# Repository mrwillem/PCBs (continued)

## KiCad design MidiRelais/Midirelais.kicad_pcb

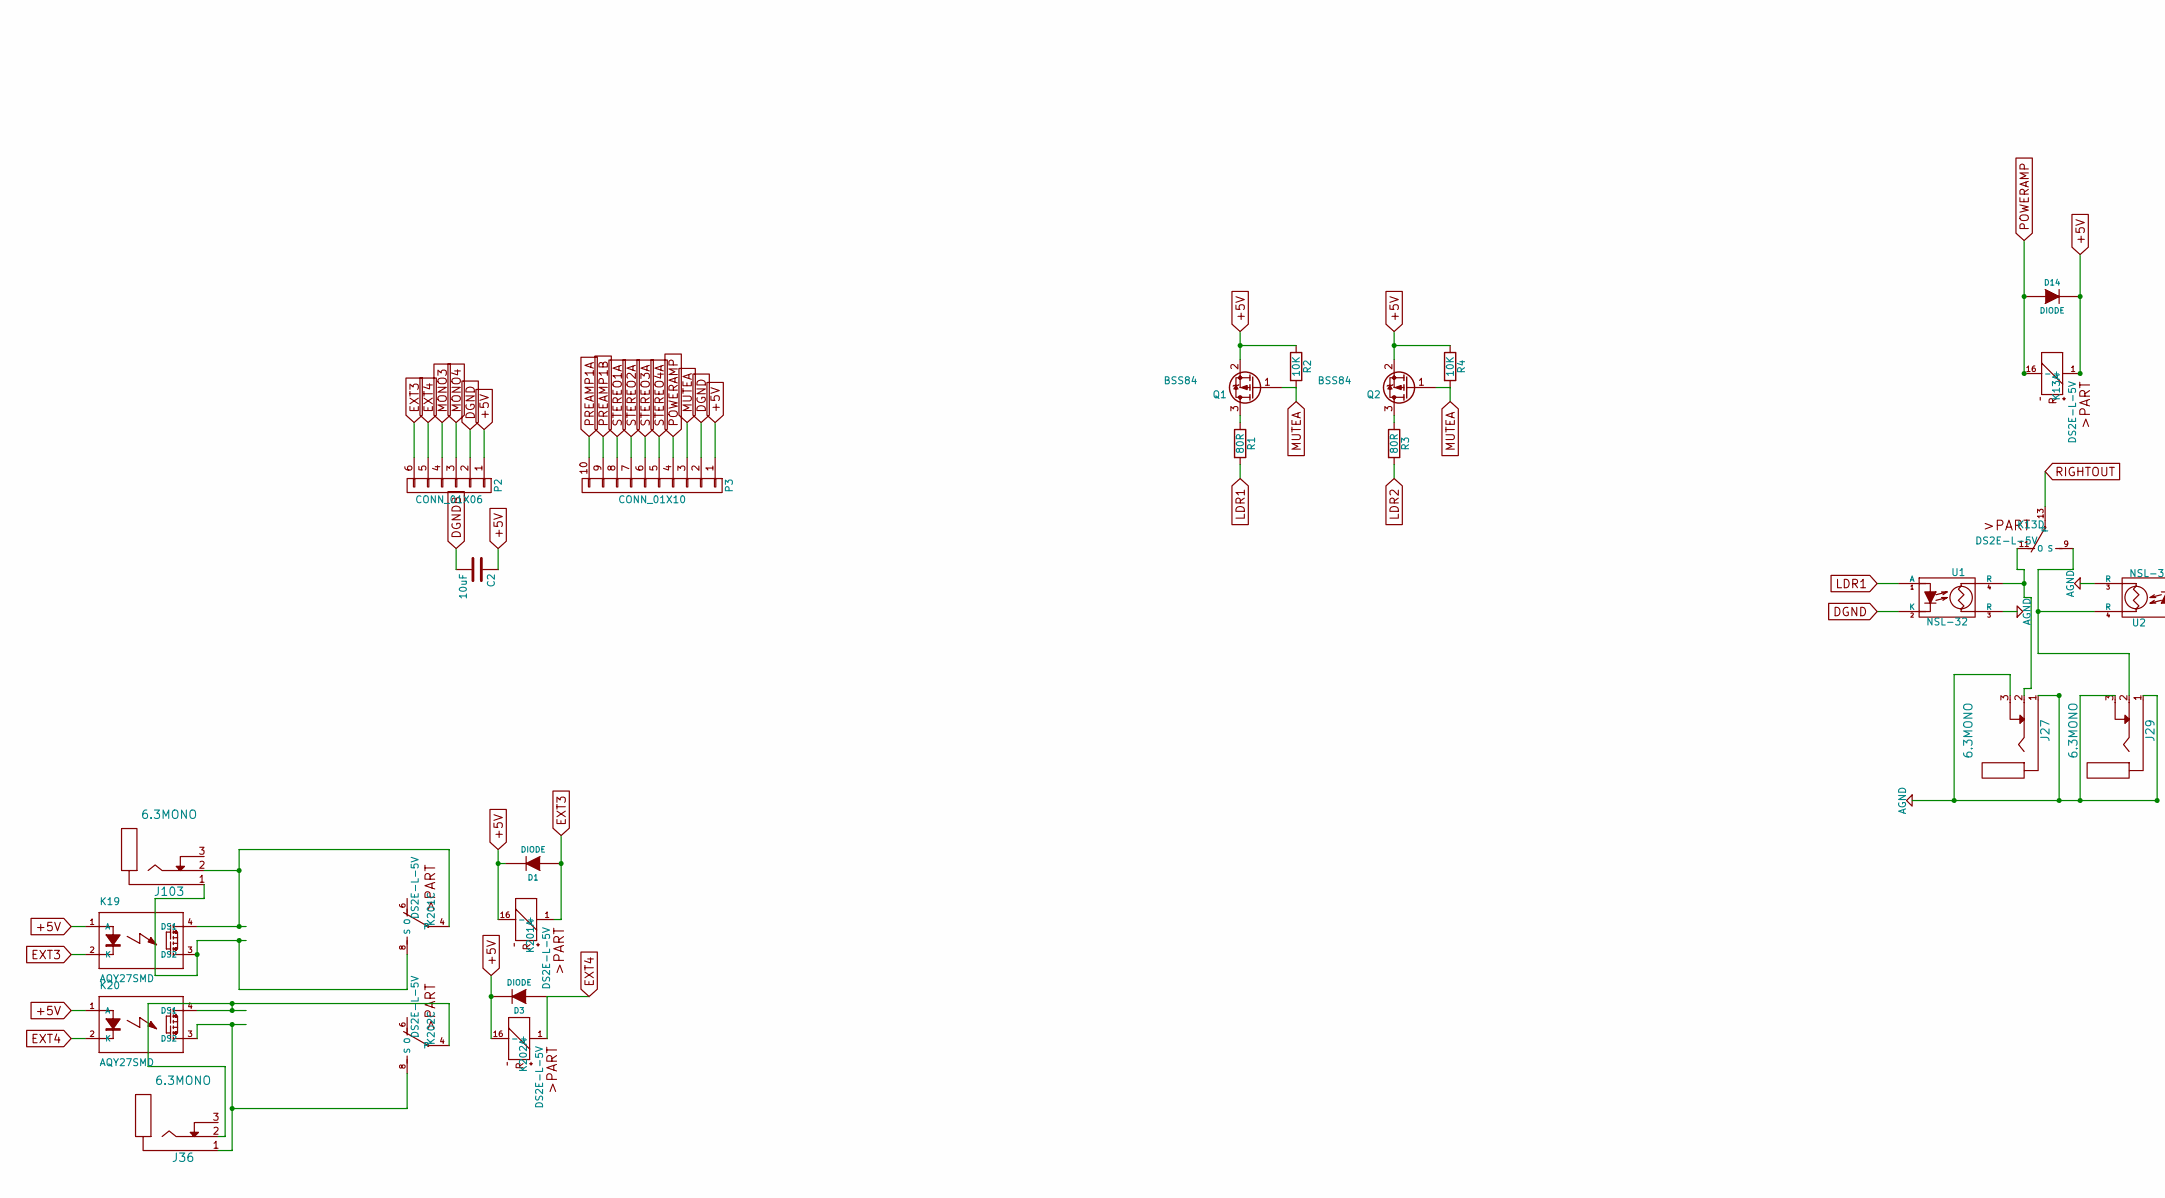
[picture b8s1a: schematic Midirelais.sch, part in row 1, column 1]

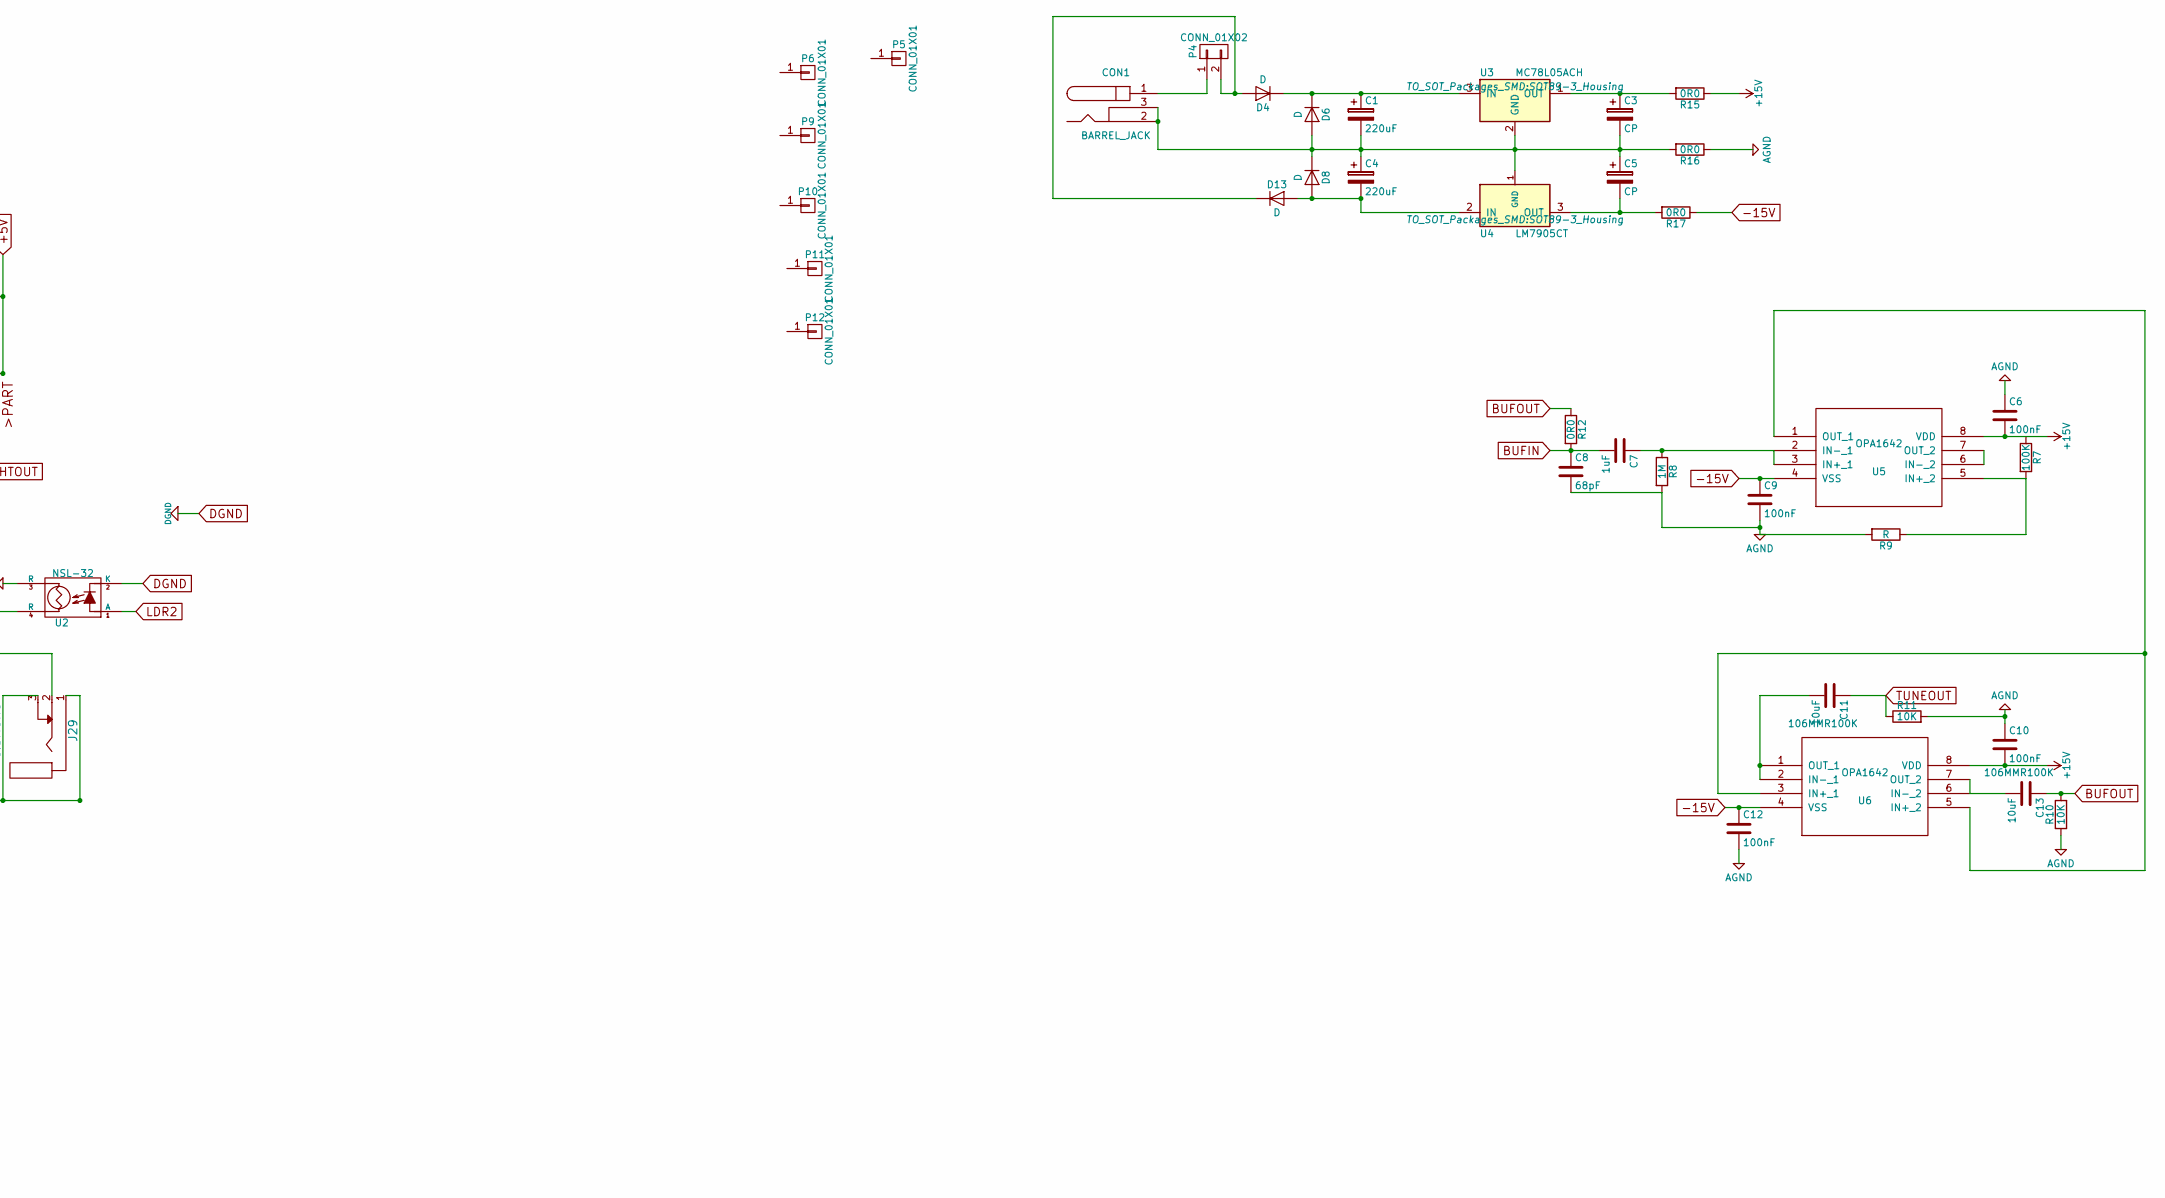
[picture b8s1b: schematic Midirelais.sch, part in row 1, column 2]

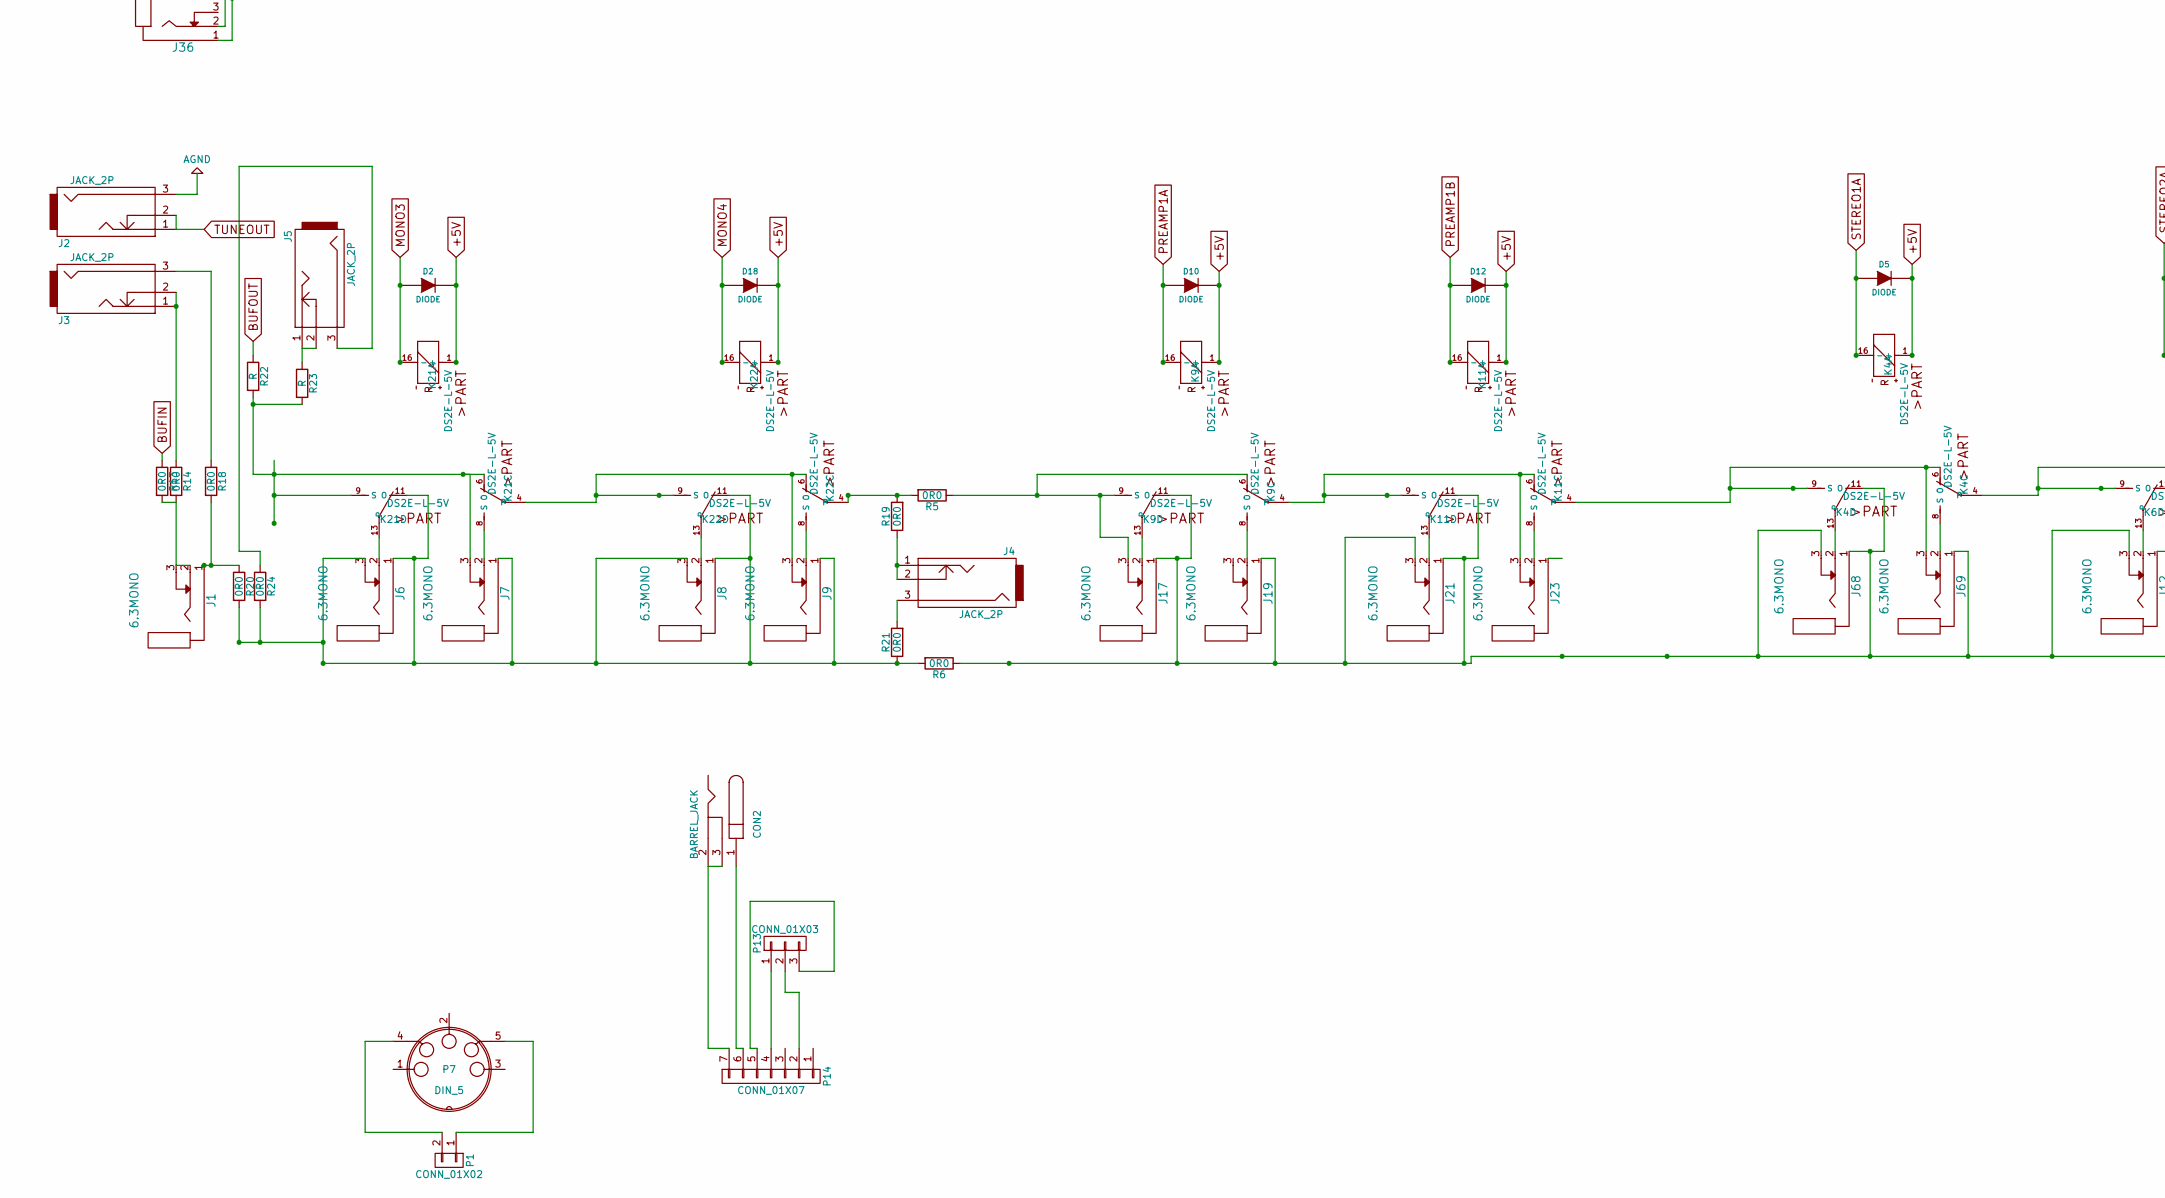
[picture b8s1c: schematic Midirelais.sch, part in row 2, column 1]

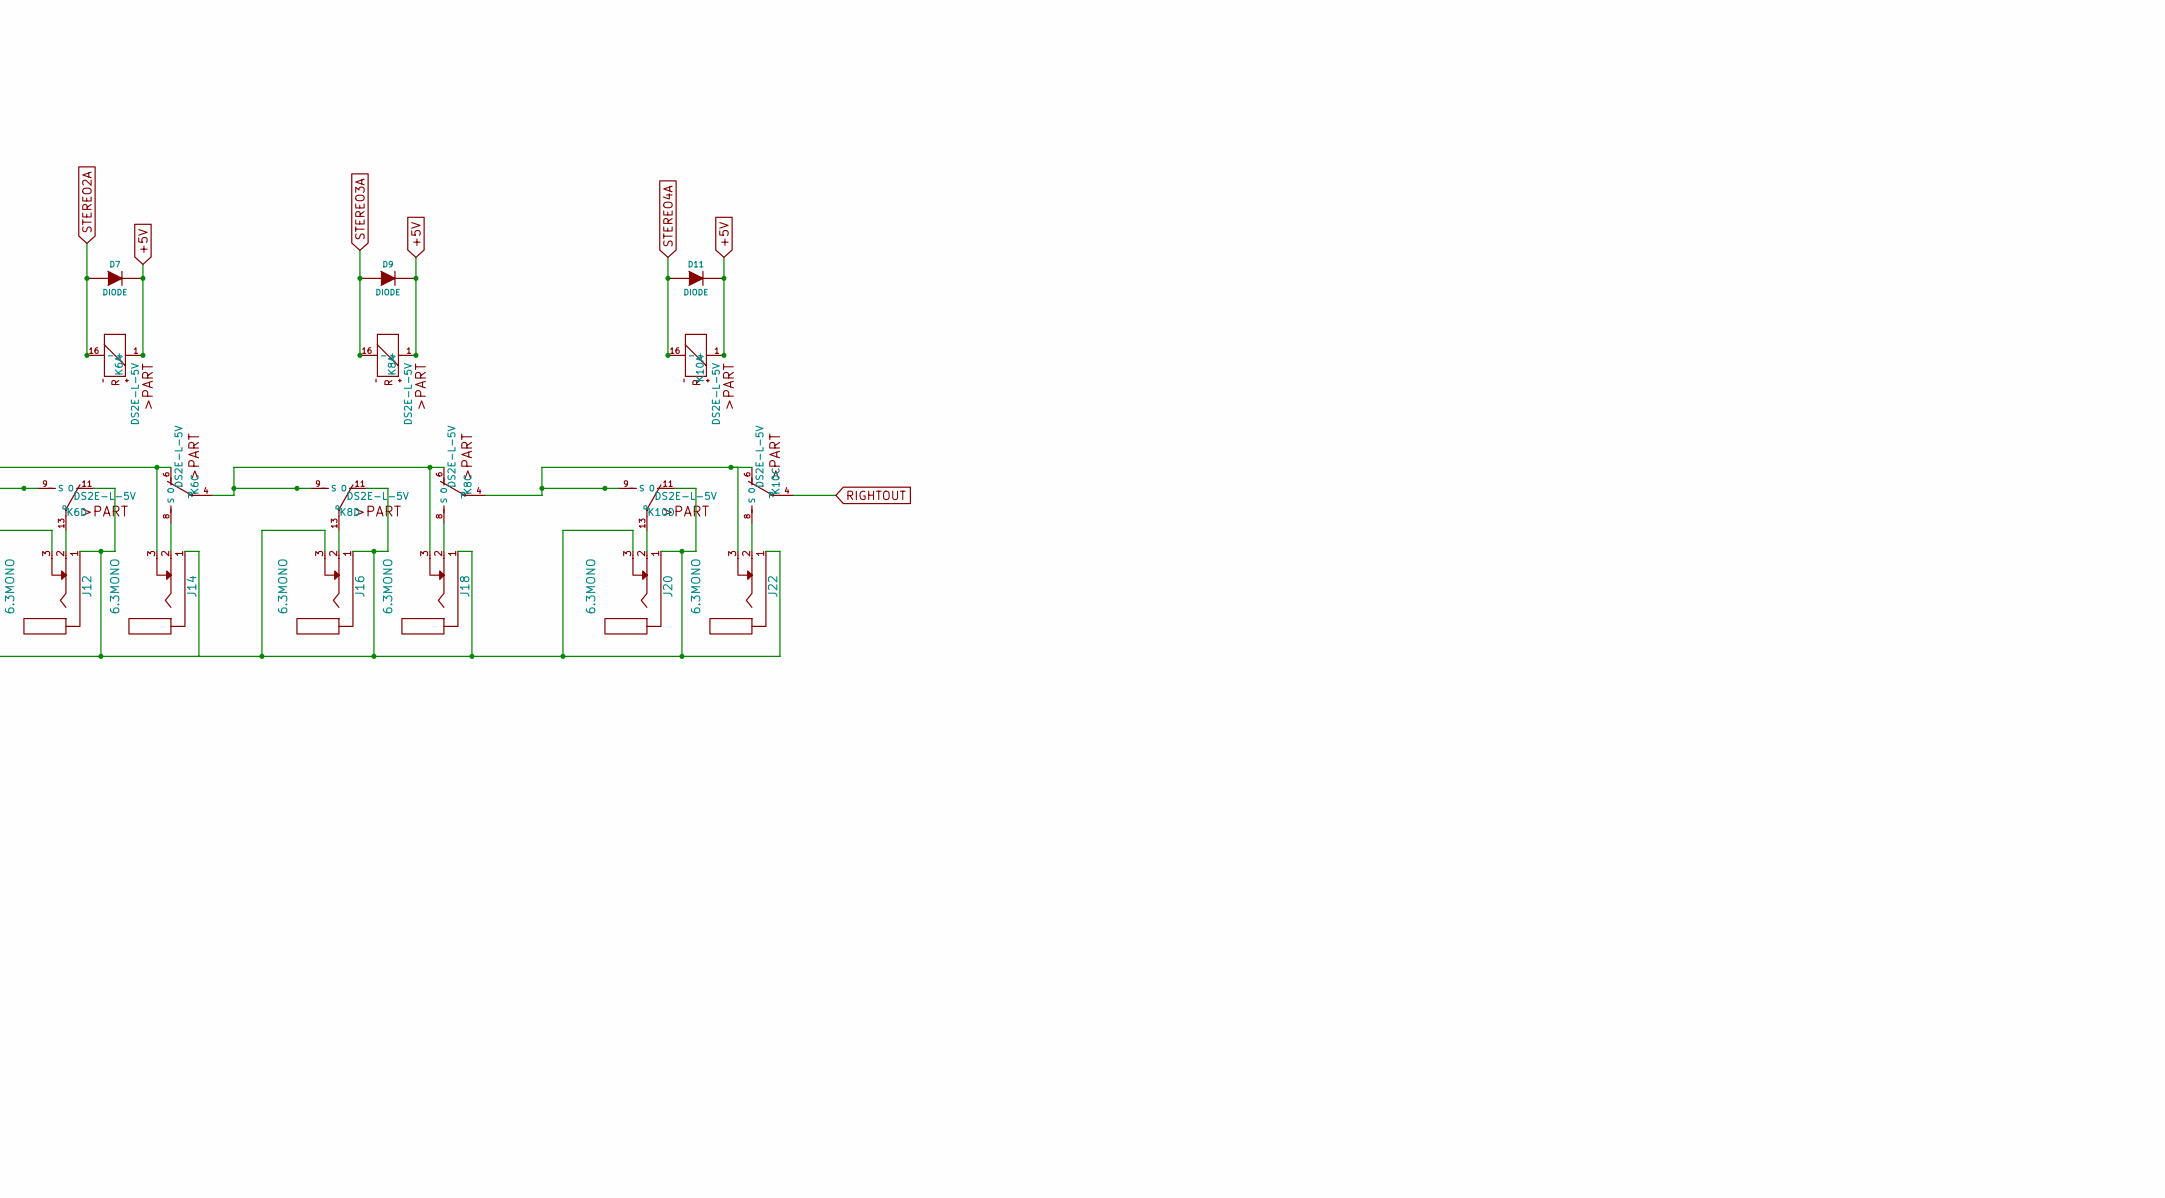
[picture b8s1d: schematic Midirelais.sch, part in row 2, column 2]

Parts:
C1, C4: 220uF; CP_Elec_6.3x7.7
C2: 10uF; C_1206
C3, C5: CP; CP_Elec_6.3x7.7
C6, C9, C10, C12: 100nF; C_0805
C7: 1uF; Capacitor-Wima-SMD2824-63v-L7,2
C8: 68pF; C_1206
C11, C13: 10uF; C_Rect_L26.5mm_W11.5mm_P22.50mm_MKS4
CON1, CON2: BARREL_JACK; BARREL_JACK_CLIFF_FC681465P
D1, D2, D3, D5, D7, D9, D10, D11, D12, D14, D18: DIODE; SOD-123-2kathode
D4, D6, D8, D13: D; D_SMA_Standard
J1, J6, J7, J8, J9, J12, J14, J16, J17, J18, J19, J20, J21, J22, J23, J27, J29, J36, J68, J69, J103: 6.3MONO; MonoPhoneJack6.3mm
J2, J3, J4, J5: JACK_2P; LUMBERG_RCA_1553_02
K4, K6, K8, K9, K10, K11, K13, K21, K22, K201, K202: DS2E-L-5V; relay-DS2E
K19, K20: AQY27SMD; Optocoupler_SMD_HandSoldering_KPC357_LTV35x_PC357_SingleCha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
P1, P4: CONN_01X02; PINHEAD1-2
P2: CONN_01X06; PINHEAD1-6
P3: CONN_01X10; PINHEAD1-10
P5, P6, P9, P10, P11, P12: CONN_01X01; MountingHole_3.2mm_M3
P7: DIN_5; CLIFF_DIN7SA
P13: CONN_01X03; PINHEAD1-3
P14: CONN_01X07; CLIFF_DIN7SA
Q1, Q2: BSS84; SOT-23
R1, R3: 80R; R_0805_HandSolder
R2, R4, R10, R11: 10K; R_0805_HandSolder
R5, R6, R12, R13, R14, R18, R19, R20, R21, R24: 0R0; R_0805_HandSolder
R7: 100K; R_0805_HandSolder
R8: 1M; R_0805_HandSolder
R9, R22, R23: R; R_0805_HandSolder
R15, R16, R17: 0R0; R_1206
U1, U2: NSL-32; Optoisolator_NSL-32
U3: MC78L05ACH; SOT89-3_Housing
U4: LM7905CT; SOT89-3_Housing
U5, U6: OPA1642; SOIC-8_3.9x4.9mm_Pitch1.27mm

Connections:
+5V: C2.1, D1.2 (K), D2.2 (K), D3.2 (K), D5.2 (K), D7.2 (K), D9.2 (K), D10.2 (K), D11.2 (K), D12.2 (K), D14.2 (K), D18.2 (K), K4.1 (+), K6.1 (+), K8.1 (+), K9.1 (+), K10.1 (+), K11.1 (+), K13.1 (+), K19.1 (A), K20.1 (A), K21.1 (+), K22.1 (+), K201.16 (-), K202.16 (-), P2.1, P3.1, Q1.2 (S), Q2.2 (S), R2.1, R4.1
+15V: C6.2, C10.2, R15.1, U5.8 (VDD), U6.8 (VDD)
-15V: C9.1, C12.1, R17.1, U5.4 (VSS), U6.4 (VSS)
AGND: C6.1, C8.2, C9.2, C10.1, C12.2, J2.3, J27.1, J27.3, J29.1, J29.3, R8.2, R9.2, R10.1, R11.2, R16.1, U1.3 (R), U2.3 (R)
BUFIN: C7.2, C8.1, R12.2, R13.1
BUFOUT: C13.1, R10.2, R12.1, R22.1
DGND: P2.2, P3.2, U1.2 (K), U2.2 (K)
DGNDB: C2.2
EXT3: D1.1 (A), K19.2 (K), K201.1 (+), P2.6
EXT4: D3.1 (A), K20.2 (K), K202.1 (+), P2.5
LDR1: R1.2, U1.1 (A)
LDR2: R3.2, U2.1 (A)
MONO3: D2.1 (A), K21.16 (-), P2.4
MONO4: D18.1 (A), K22.16 (-), P2.3
MUTEA: P3.3, Q1.1 (G), Q2.1 (G), R2.2, R4.2
unnamed: C1.1, D4.1 (K), D6.1 (K), U3.3 (IN)
unnamed: C1.2, C3.2, C4.1, C5.1, CON1.2, CON1.3, D6.2 (A), D8.1 (K), R16.2, U3.2 (GND), U4.1 (GND)
unnamed: C3.1, R15.2, U3.1 (OUT)
unnamed: C4.2, D8.2 (A), D13.2 (A), U4.2 (IN)
unnamed: C5.2, R17.2, U4.3 (OUT)
unnamed: C7.1, R8.1, U5.2 (IN-_1), U5.3 (IN+_1)
unnamed: C11.2, U6.1 (OUT_1), U6.2 (IN-_1)
unnamed: C13.2, U6.6 (IN-_2), U6.7 (OUT_2)
unnamed: CON1.1, P4.1
unnamed: CON2.1, P14.6
unnamed: CON2.2, CON2.3, P14.7
unnamed: D4.2 (A), D13.1 (K), P4.2
unnamed: J1.1, R18.2, R20.1
unnamed: J1.2, J1.3, R13.2, R14.2
unnamed: J3.1, J3.2, R14.1
unnamed: J3.3, R18.1
unnamed: J4.1, J4.2, R19.1
unnamed: J4.3, R21.2
unnamed: J5.1, J5.2, R23.1
unnamed: J5.3, R24.1
unnamed: J6.1, J6.3, J7.1, J8.1, J8.3, J9.1, K21.11 (O), K22.11 (O), R6.2, R20.2, R21.1, R24.2
unnamed: J6.2, K21.13
unnamed: J7.2, K21.8 (S)
unnamed: J7.3, K21.6 (O), K21.9 (S), R22.2, R23.2
unnamed: J8.2, K22.13
unnamed: J9.2, K22.8 (S)
unnamed: J9.3, K21.4, K22.6 (O), K22.9 (S)
unnamed: J12.1, J12.3, J16.1, J16.3, J17.1, J18.1, J19.1, J20.1, J20.3, J21.1, J21.3, J22.1, J68.1, J68.3, J69.1, K4.11 (O), K6.11 (O), K8.11 (O), K9.11 (O), K10.11 (O), K11.11 (O), R6.1
unnamed: J12.2, K6.13
unnamed: J14.2, K6.8 (S)
unnamed: J14.3, K4.4, K6.6 (O), K6.9 (S)
unnamed: J16.2, K8.13
unnamed: J17.2, K9.13
unnamed: J17.3, K9.6 (O), K9.9 (S), R5.1
unnamed: J18.2, K8.8 (S)
unnamed: J18.3, K6.4, K8.6 (O), K8.9 (S)
unnamed: J19.2, K9.8 (S)
unnamed: J20.2, K10.13
unnamed: J21.2, K11.13
unnamed: J22.2, K10.8 (S)
unnamed: J22.3, K8.4, K10.6 (O), K10.9 (S)
unnamed: J23.2, K11.8 (S)
unnamed: J23.3, K9.4, K11.6 (O), K11.9 (S)
unnamed: J27.2, K13.11 (O), U1.4 (R)
unnamed: J29.2, K13.9 (S), U2.4 (R)
unnamed: J36.1, K20.3 (DS2), K202.8 (S)
unnamed: J36.2, K20.4 (DS1), K202.4
unnamed: J68.2, K4.13
unnamed: J69.2, K4.8 (S)
unnamed: J69.3, K4.6 (O), K4.9 (S), K11.4
unnamed: J103.1, K19.3 (DS2), K201.8 (S)
unnamed: J103.2, K19.4 (DS1), K201.4
unnamed: K22.4, R5.2, R19.2
unnamed: P1.1, P7.5
unnamed: P1.2, P7.4
unnamed: P13.1, P14.4
unnamed: P13.2, P14.2
unnamed: P13.3, P14.5
unnamed: Q1.3 (D), R1.1
unnamed: Q2.3 (D), R3.1
unnamed: R7.2, R9.1, U5.5 (IN+_2)
unnamed: U5.1 (OUT_1), U6.3 (IN+_1), U6.5 (IN+_2)
unnamed: U5.6 (IN-_2), U5.7 (OUT_2)
POWERAMP: D14.1 (A), K13.16 (-), P3.4
PREAMP1A: D10.1 (A), K9.16 (-), P3.10
PREAMP1B: D12.1 (A), K11.16 (-), P3.9
RIGHTOUT: K10.4, K13.13
STEREO1A: D5.1 (A), K4.16 (-), P3.8
STEREO2A: D7.1 (A), K6.16 (-), P3.7
STEREO3A: D9.1 (A), K8.16 (-), P3.6
STEREO4A: D11.1 (A), K10.16 (-), P3.5
TUNEOUT: C11.1, J2.1, J2.2, R11.1

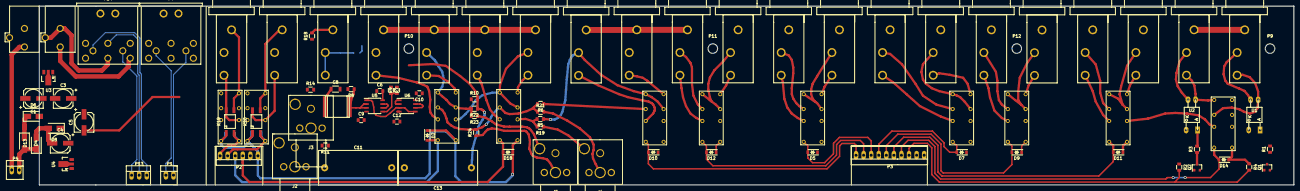
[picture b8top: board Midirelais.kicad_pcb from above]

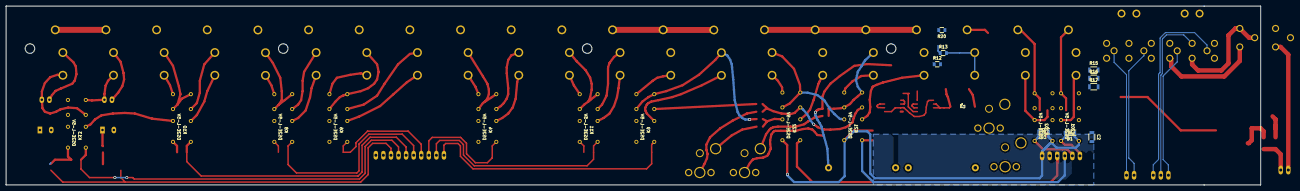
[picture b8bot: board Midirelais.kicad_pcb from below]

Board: 2 copper layers, 421.0 x 60.0 mm, 113 parts (9 on the bottom side), 86 nets.
